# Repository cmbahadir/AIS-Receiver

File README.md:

# AIS Receiver by CMB

Please be aware that this project is still under construction. 

Required: https://github.com/KiCad/kicad-library

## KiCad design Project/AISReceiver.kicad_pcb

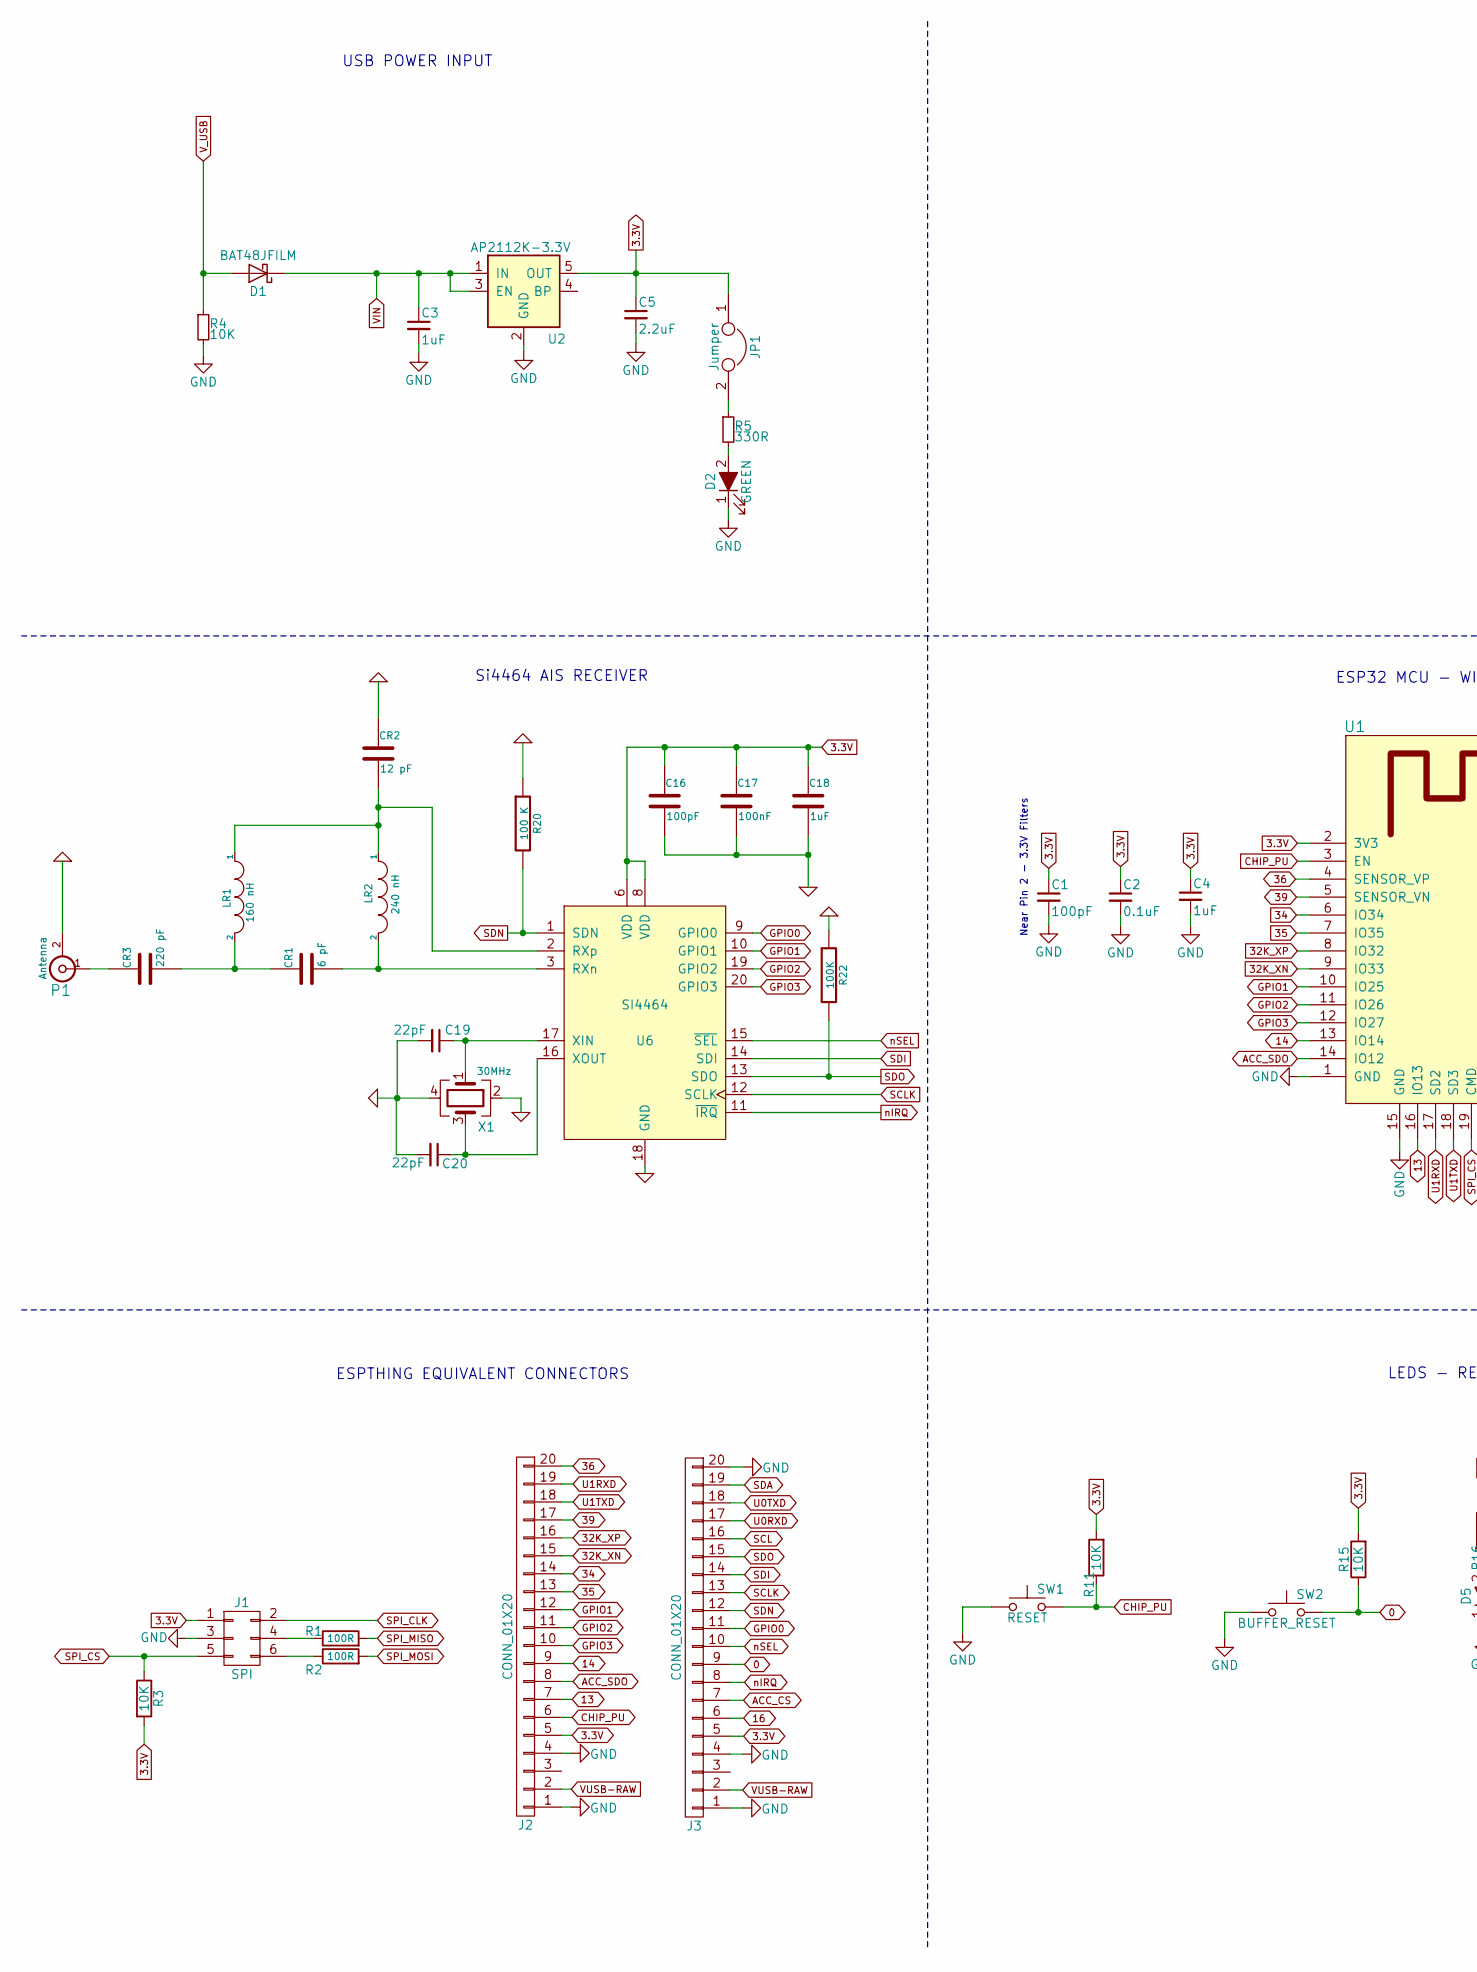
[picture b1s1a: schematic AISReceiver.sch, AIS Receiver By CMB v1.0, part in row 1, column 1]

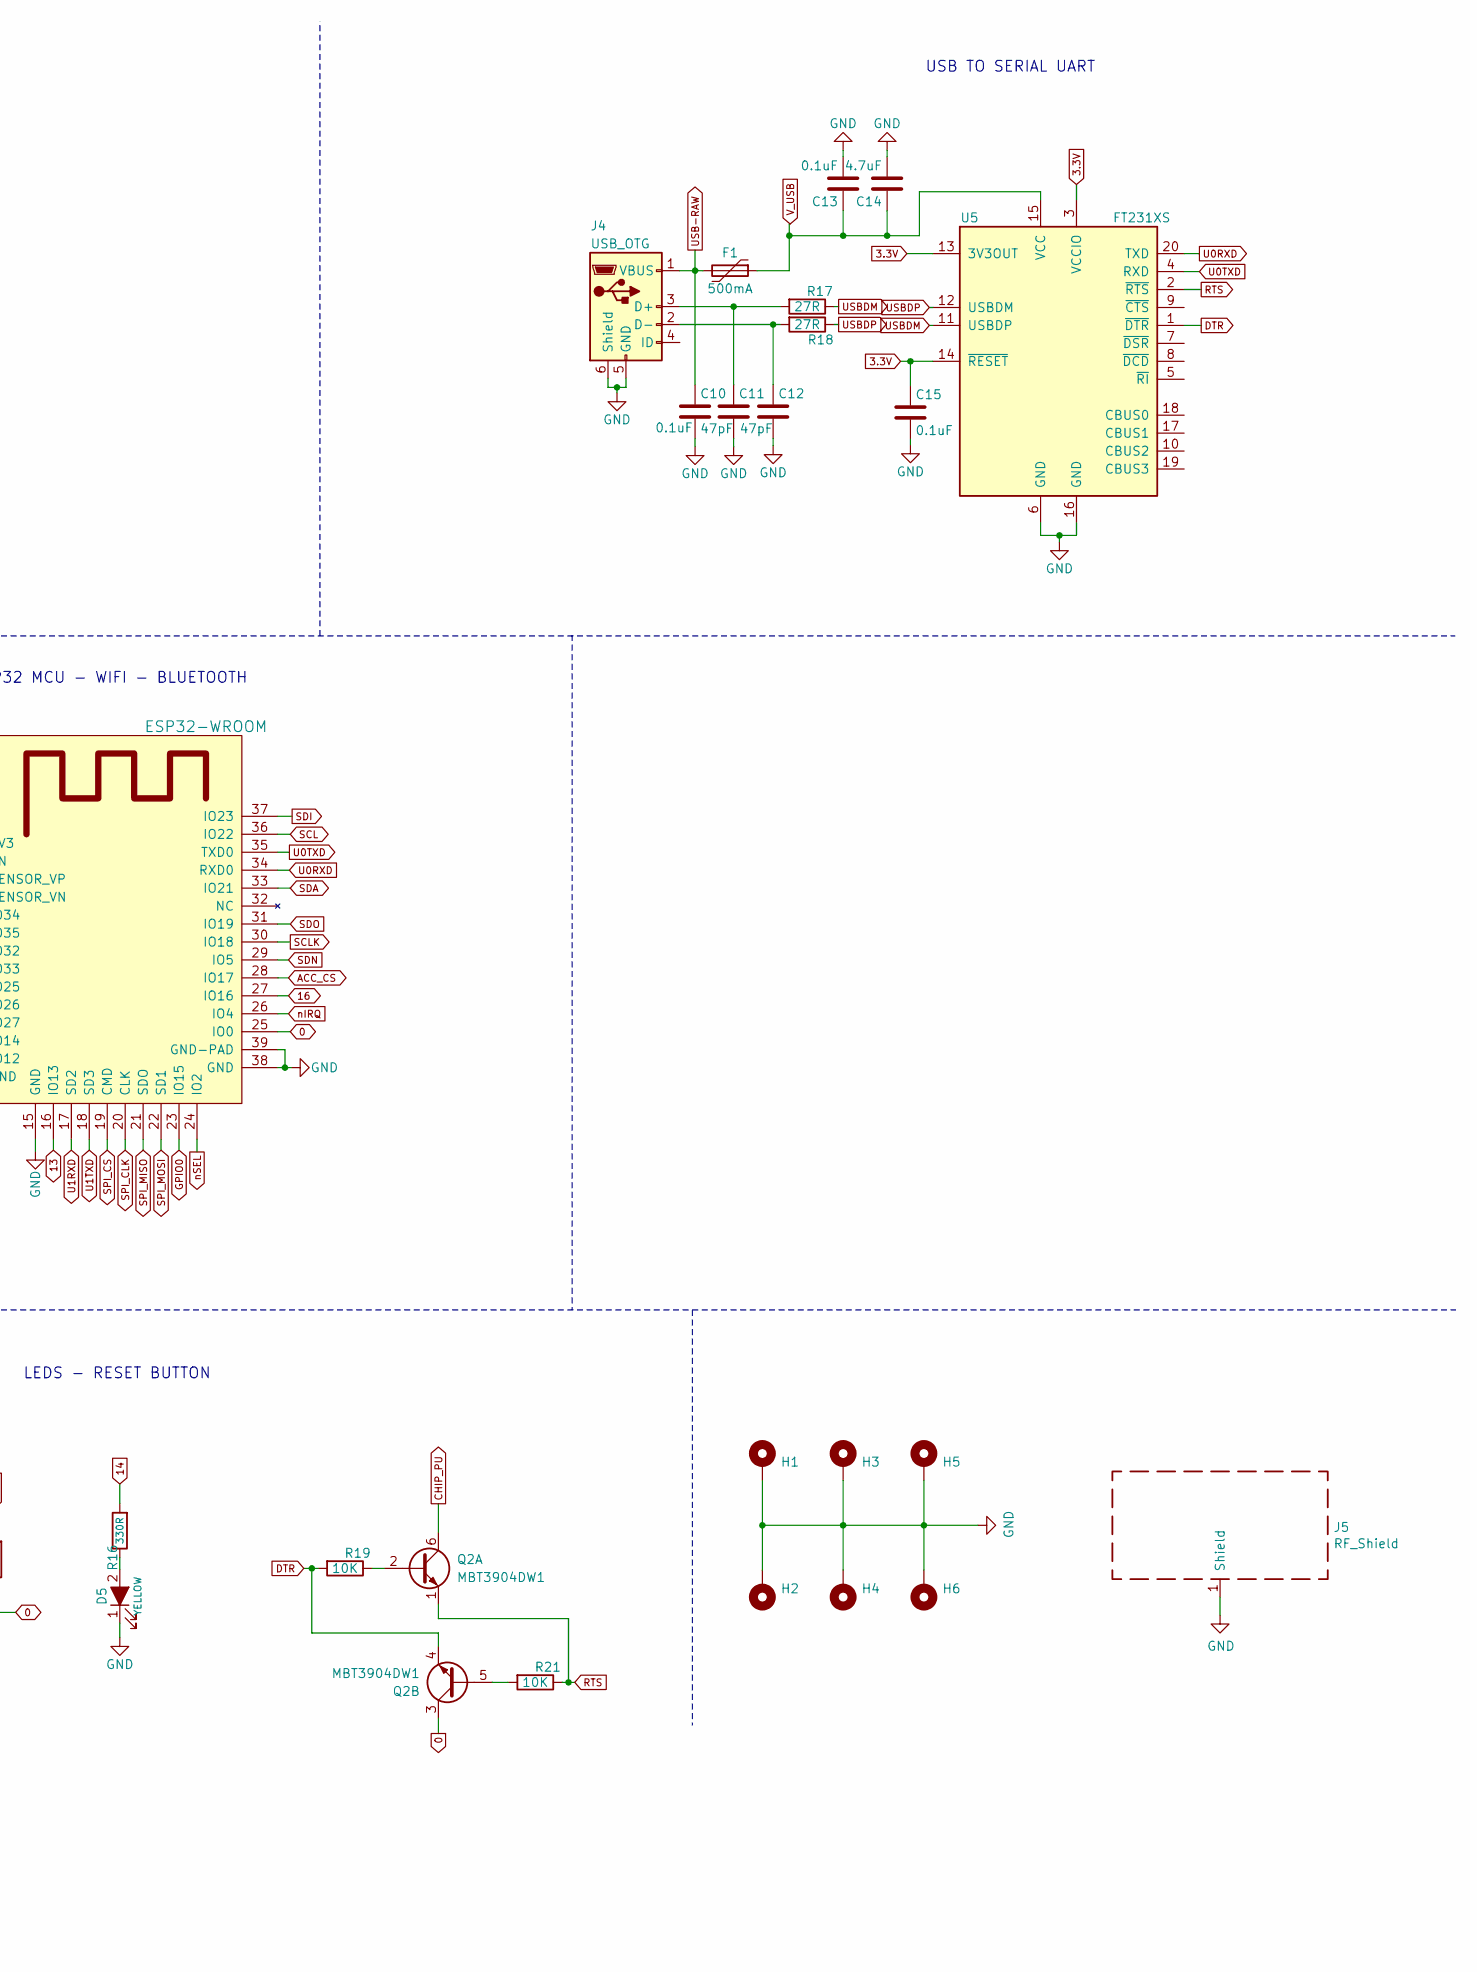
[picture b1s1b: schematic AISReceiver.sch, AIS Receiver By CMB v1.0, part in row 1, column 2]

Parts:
C1, C16: 100pF; C_0603_1608Metric_Pad1.08x0.95mm_HandSolder
C2, C10, C13, C15: 0.1uF; C_0603_1608Metric_Pad1.08x0.95mm_HandSolder
C3, C4, C18: 1uF; C_0603_1608Metric_Pad1.08x0.95mm_HandSolder
C5: 2.2uF; C_0603_1608Metric_Pad1.08x0.95mm_HandSolder
C11, C12: 47pF; C_0603_1608Metric_Pad1.08x0.95mm_HandSolder
C14: 4.7uF; C_0603_1608Metric_Pad1.08x0.95mm_HandSolder
C17: 100nF; C_0603_1608Metric_Pad1.08x0.95mm_HandSolder
C19, C20: 22pF; C_0603_1608Metric_Pad1.08x0.95mm_HandSolder
CR1: 6 pF; C_0603_1608Metric_Pad1.08x0.95mm_HandSolder
CR2: 12 pF; C_0603_1608Metric_Pad1.08x0.95mm_HandSolder
CR3: 220 pF; C_1210_3225Metric_Pad1.33x2.70mm_HandSolder
D1: BAT48JFILM; D_SOD-323
D2: GREEN; LED_D3.0mm_Clear
D5: YELLOW; LED_D3.0mm_Clear
F1: 500mA; 1206
H1, H2, H3, H4, H5, H6: MountingHole_Pad; Mounting_Wuerth_WA-SMSI-M1.6_H1.5mm_9774015633
J1: SPI; PinHeader_2x03_P2.54mm_Horizontal
J2, J3: CONN_01X20; PinHeader_2x10_P2.54mm_Vertical
J4: USB_OTG; USB_Micro-B
J5: RF_Shield; Wuerth_36103205_20x20mm
JP1: Jumper; C_0603_1608Metric_Pad1.08x0.95mm_HandSolder
LR1: 160 nH; C_0805_2012Metric_Pad1.18x1.45mm_HandSolder
LR2: 240 nH; C_0402_1005Metric_Pad0.74x0.62mm_HandSolder
P1: Antenna; SMA_Amphenol_132134_Vertical
Q2: MBT3904DW1; SOT-363
R1, R2: 100R; R_0603_1608Metric_Pad0.98x0.95mm_HandSolder
R3, R4, R11, R15, R19, R21: 10K; R_0603_1608Metric_Pad0.98x0.95mm_HandSolder
R5, R16: 330R; R_0603_1608Metric_Pad0.98x0.95mm_HandSolder
R17, R18: 27R; R_0603_1608Metric_Pad0.98x0.95mm_HandSolder
R20: 100 K; R_0603_1608Metric_Pad0.98x0.95mm_HandSolder
R22: 100K; R_0603_1608Metric_Pad0.98x0.95mm_HandSolder
SW1: RESET; SW_SPST_B3SL-1022P
SW2: BUFFER_RESET; SW_SPST_B3SL-1022P
U1: ESP32-WROOM; ESP32-WROOM-32
U2: AP2112K-3.3V; SOT-23-5_HandSoldering
U5: FT231XS; SSOP_20
U6: SI4464; Si4464
X1: 30MHz; Crystal_SMD_0603-4Pin_6.0x3.5mm_HandSoldering

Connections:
0: J3.9, Q2.3 (C2), R15.1, SW2.2, U1.25 (IO0)
3.3V: C1.1, C2.1, C4.1, C5.1, C15.1, C16.1, C17.1, C18.1, J1.1, J2.5, J3.5, JP1.1, R3.2, R11.2, R15.2, U1.2 (3V3), U2.5 (OUT), U5.3 (VCCIO), U5.13 (3V3OUT), U5.14 (~RESET), U6.6 (VDD), U6.8 (VDD)
13: J2.7, U1.16 (IO13)
14: J2.9, R16.2, U1.13 (IO14)
16: J3.6, U1.27 (IO16)
32K_XN: J2.15, U1.9 (IO33)
32K_XP: J2.16, U1.8 (IO32)
34: J2.14, U1.6 (IO34)
35: J2.13, U1.7 (IO35)
36: J2.20, U1.4 (SENSOR_VP)
39: J2.17, U1.5 (SENSOR_VN)
ACC_CS: J3.7, U1.28 (IO17)
ACC_SDO: J2.8, U1.14 (IO12)
CHIP_PU: J2.6, Q2.6 (C1), R11.1, SW1.2, U1.3 (EN)
DTR: Q2.4 (E2), R19.2, U5.1 (~DTR)
GND: C1.2, C2.2, C3.2, C4.2, C5.2, C10.2, C11.2, C12.2, C13.2, C14.2, C15.2, C16.2, C17.2, C18.2, C19.2, CR2.1, D2.1 (K), D5.1 (K), H1.1, H2.1, H3.1, H4.1, H5.1, H6.1, J1.3, J2.1, J2.4, J3.1, J3.4, J3.20, J4.5 (GND), J4.6 (Shield), J5.1, P1.2 (Ext), R4.2, R20.1, R22.1, SW1.1, SW2.1, U1.1 (GND), U1.15 (GND), U1.38 (GND), U1.39 (GND-PAD), U2.2 (GND), U5.6 (GND), U5.16 (GND), U6.18 (GND), X1.2, X1.4; also elsewhere on the board
GPIO0: J3.11, U1.23 (IO15), U6.9 (GPIO0)
GPIO1: J2.12, U1.10 (IO25), U6.10 (GPIO1)
GPIO2: J2.11, U1.11 (IO26), U6.19 (GPIO2)
GPIO3: J2.10, U1.12 (IO27), U6.20 (GPIO3)
unnamed: C11.1, J4.3 (D+), R17.2
unnamed: C12.1, J4.2 (D-), R18.2
unnamed: C19.1, U6.17 (XIN), X1.1
unnamed: C20.1, U6.16 (XOUT), X1.3
unnamed: CR1.1, CR3.2, LR1.2
unnamed: CR1.2, LR2.2, U6.3 (RXn)
unnamed: CR2.2, LR1.1, LR2.1, U6.2 (RXp)
unnamed: CR3.1, P1.1 (In)
unnamed: D2.2 (A), R5.2
unnamed: D5.2 (A), R16.1
unnamed: J1.4, R1.1
unnamed: J1.6, R2.1
unnamed: JP1.2, R5.1
unnamed: Q2.2 (B1), R19.1
unnamed: Q2.5 (B2), R21.2
RTS: Q2.1 (E1), R21.1, U5.2 (~RTS)
SCL: J3.16, U1.36 (IO22)
SCLK: J3.13, U1.30 (IO18), U6.12 (SCLK)
SDA: J3.19, U1.33 (IO21)
SDI: J3.14, U1.37 (IO23), U6.14 (SDI)
SDN: J3.12, R20.2, U1.29 (IO5), U6.1 (SDN)
SDO: J3.15, R22.2, U1.31 (IO19), U6.13 (SDO)
SPI_CLK: J1.2, U1.20 (CLK)
SPI_CS: J1.5, R3.1, U1.19 (CMD)
SPI_MISO: R1.2, U1.21 (SDO)
SPI_MOSI: R2.2, U1.22 (SD1)
U0RXD: J3.17, U1.34 (RXD0), U5.20 (TXD)
U0TXD: J3.18, U1.35 (TXD0), U5.4 (RXD)
U1RXD: J2.19, U1.17 (SD2)
U1TXD: J2.18, U1.18 (SD3)
USB-RAW: C10.1, F1.2, J4.1 (VBUS)
USBDM: R17.1, U5.11 (USBDP)
USBDP: R18.1, U5.12 (USBDM)
VIN: C3.1, D1.1 (K), U2.1 (IN), U2.3 (EN)
VUSB-RAW: J2.2, J3.2
V_USB: C13.1, C14.1, D1.2 (A), F1.1, R4.1, U5.15 (VCC)
nIRQ: J3.8, U1.26 (IO4), U6.11 (~IRQ)
nSEL: J3.10, U1.24 (IO2), U6.15 (~SEL)

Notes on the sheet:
Near Pin 2 - 3.3V Filters
USB POWER INPUT
USB TO SERIAL UART
ESP32 MCU - WIFI - BLUETOOTH
Si4464 AIS RECEIVER
ESPTHING EQUIVALENT CONNECTORS
LEDS - RESET BUTTON

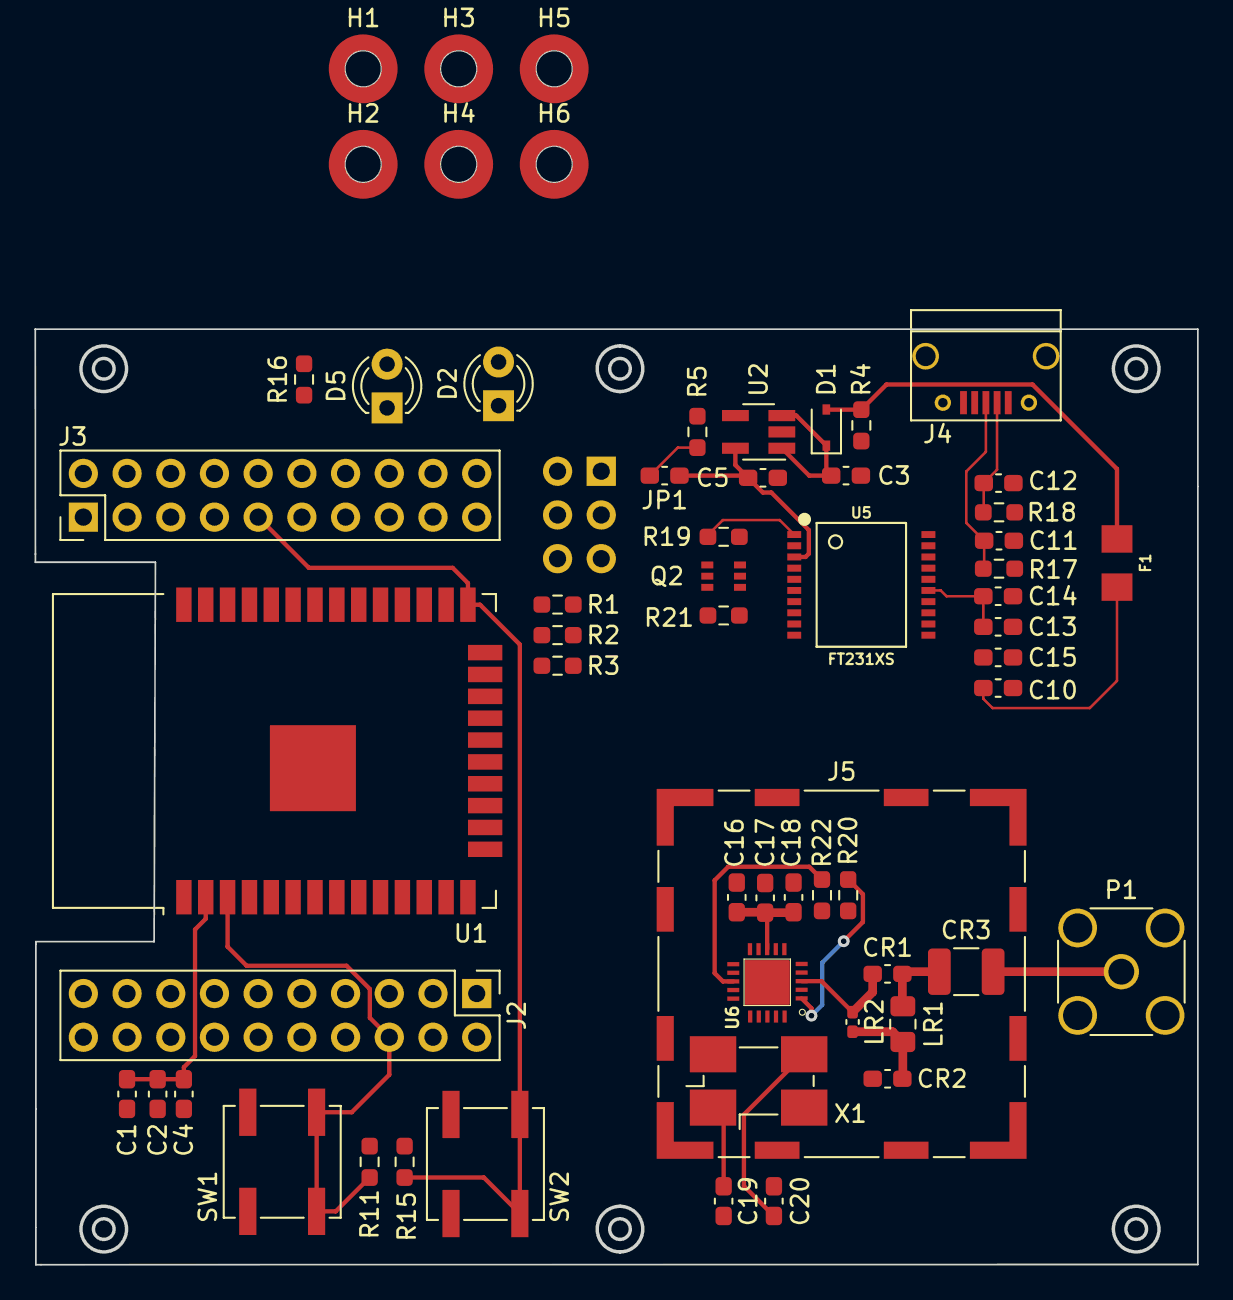
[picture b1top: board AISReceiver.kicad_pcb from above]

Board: 2 copper layers, 67.6 x 54.4 mm, 61 parts (1 on the bottom side), 58 nets.

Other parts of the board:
J5#2: RF_Shield; Wuerth_36103205_20x20mm

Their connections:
GND: J5#2.1; also elsewhere on the board

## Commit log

2018-04-05 First Commit - Hardware Files - Kicad Project
2021-01-17 AIS specific board.
2021-01-17 Initial tracing.
